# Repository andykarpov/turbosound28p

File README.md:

# Turbosound AVR AY Emul v1.0

TurboSound Emulator on 2x Atmega8A chips based on http://www.avray.ru project.

## How to upload the firmware
Due to there is no room for ISP connectors on the board, you need to solder a few wires directly on the board and connect them with your programmer:
- GND, VCC and RESET signals 
- CK, SO, SI as SCLK, MISO and MOSI signals 
- Do not forget to bridge solder jumpers

### Uploading:

Use avrdude and USBAsp programmer to upload firmware for each chip:

avrdude -p atmega8 -c USBasp -U flash:w:emul_230_turbosound_chip0.hex -U eeprom:w:Conf_parallel_24MHz_1_75Mhz.hex -U lfuse:w:0xCE:m -U hfuse:w:0xCF:m

avrdude -p atmega8 -c USBasp -U flash:w:emul_230_turbosound_chip1.hex -U eeprom:w:Conf_parallel_24MHz_1_75Mhz.hex -U lfuse:w:0xCE:m -U hfuse:w:0xCF:m

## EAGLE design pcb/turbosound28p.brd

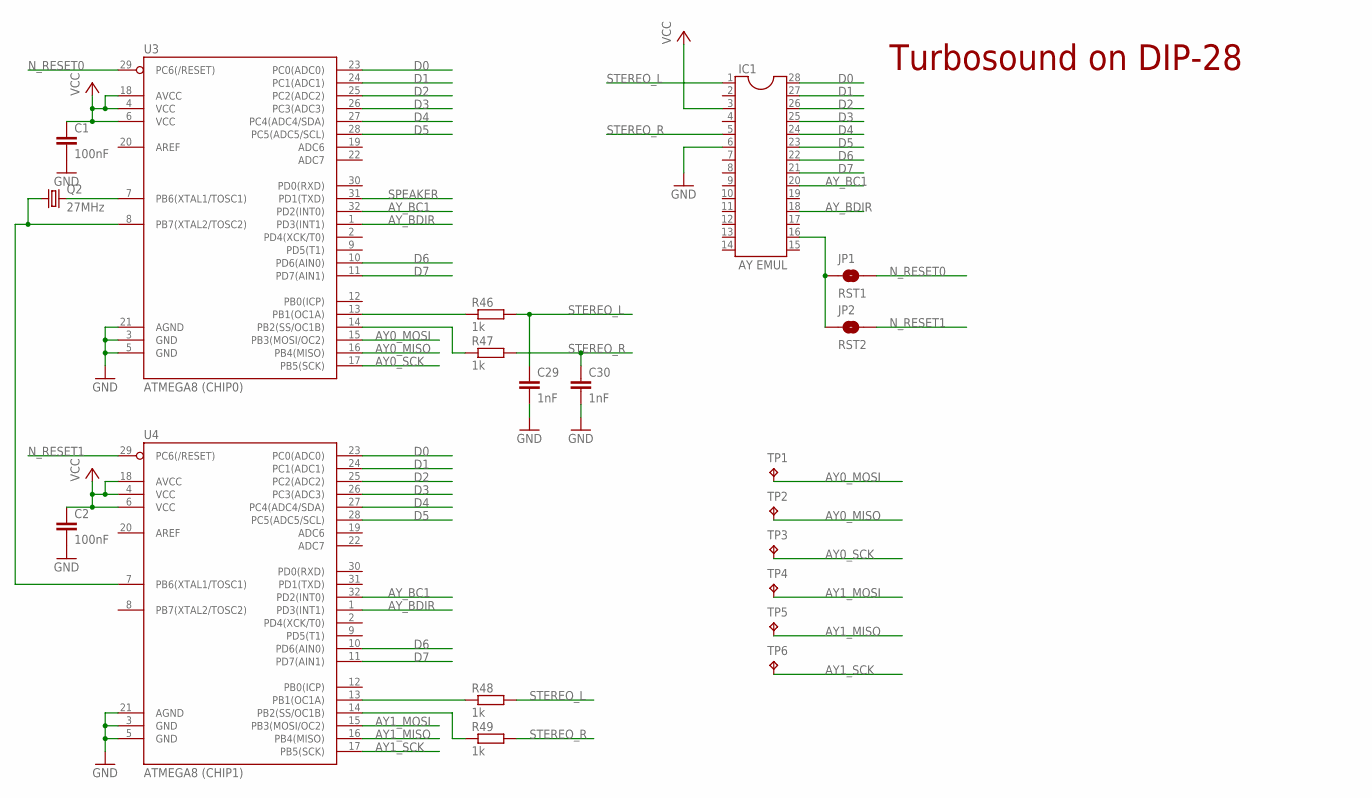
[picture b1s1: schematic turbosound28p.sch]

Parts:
C1, C2: 100nF; C0805
C29, C30: 1nF; C0805
IC1: AY EMUL; DIL28-6
JP1: RST1; SMT-JUMPER_2_NO_SILK
JP2: RST2; SMT-JUMPER_2_NO_SILK
Q2: 27MHz; HC49/S
R46, R47, R48, R49: 1k; R0805
TP1, TP2, TP3, TP4, TP5, TP6: TPB1,27; B1,27
U3: ATMEGA8 (CHIP0); TQFP32-08
U4: ATMEGA8 (CHIP1); TQFP32-08

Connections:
AY0_MISO: TP2.TP, U3.16 (PB4(MISO))
AY0_MOSI: TP1.TP, U3.15 (PB3(MOSI/OC2))
AY0_SCK: TP3.TP, U3.17 (PB5(SCK))
AY1_MISO: TP5.TP, U4.16 (PB4(MISO))
AY1_MOSI: TP4.TP, U4.15 (PB3(MOSI/OC2))
AY1_SCK: TP6.TP, U4.17 (PB5(SCK))
AY_BC1: IC1.20, U3.32 (PD2(INT0)), U4.32 (PD2(INT0))
AY_BDIR: IC1.18, U3.1 (PD3(INT1)), U4.1 (PD3(INT1))
D0: IC1.28, U3.23 (PC0(ADC0)), U4.23 (PC0(ADC0))
D1: IC1.27, U3.24 (PC1(ADC1)), U4.24 (PC1(ADC1))
D2: IC1.26, U3.25 (PC2(ADC2)), U4.25 (PC2(ADC2))
D3: IC1.25, U3.26 (PC3(ADC3)), U4.26 (PC3(ADC3))
D4: IC1.24, U3.27 (PC4(ADC4/SDA)), U4.27 (PC4(ADC4/SDA))
D5: IC1.23, U3.28 (PC5(ADC5/SCL)), U4.28 (PC5(ADC5/SCL))
D6: IC1.22, U3.10 (PD6(AIN0)), U4.10 (PD6(AIN0))
D7: IC1.21, U3.11 (PD7(AIN1)), U4.11 (PD7(AIN1))
GND: C1.2, C2.2, C29.2, C30.2, IC1.6, U3.3 (GND), U3.5 (GND), U3.21 (AGND), U4.3 (GND), U4.5 (GND), U4.21 (AGND)
unnamed: IC1.16, JP1.1, JP2.1
unnamed: R46.1, U3.13 (PB1(OC1A))
unnamed: R47.1, U3.14 (PB2(SS/OC1B))
unnamed: Q2.2, U3.7 (PB6(XTAL1/TOSC1))
unnamed: Q2.1, U3.8 (PB7(XTAL2/TOSC2)), U4.7 (PB6(XTAL1/TOSC1))
unnamed: R48.1, U4.13 (PB1(OC1A))
unnamed: R49.1, U4.14 (PB2(SS/OC1B))
N_RESET0: JP1.2, U3.29 (PC6(/RESET))
N_RESET1: JP2.2, U4.29 (PC6(/RESET))
SPEAKER: U3.31 (PD1(TXD))
STEREO_L: C29.1, IC1.1, R46.2, R48.2
STEREO_R: C30.1, IC1.5, R47.2, R49.2
VCC: C1.1, C2.1, IC1.3, U3.4 (VCC), U3.6 (VCC), U3.18 (AVCC), U4.4 (VCC), U4.6 (VCC), U4.18 (AVCC)

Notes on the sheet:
Turbosound on DIP-28

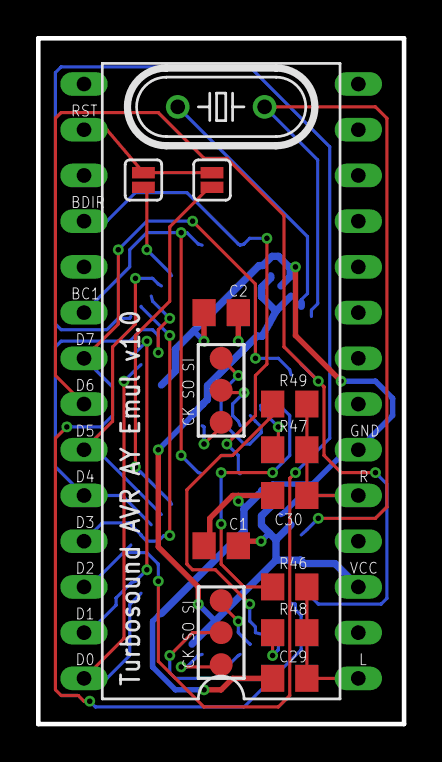
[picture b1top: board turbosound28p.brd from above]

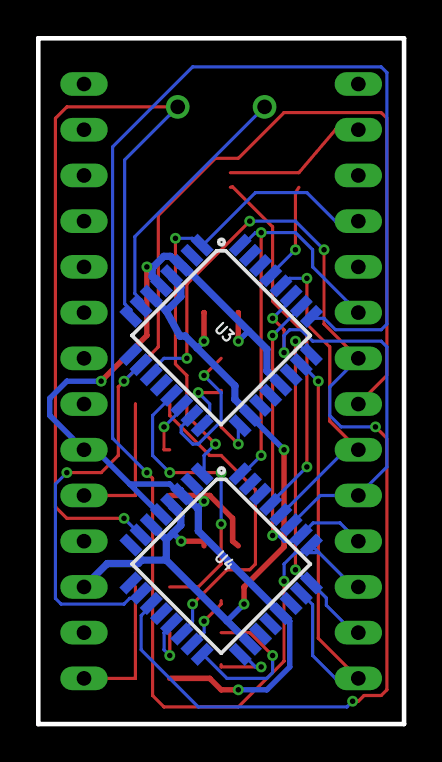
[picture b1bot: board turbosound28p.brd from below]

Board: 2 copper layers, 20.3 x 38.1 mm, 20 parts (2 on the bottom side), 29 nets.

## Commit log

2019-03-05 README
2019-03-05 Turbosound firmware
2019-03-05 PCB sources and gerbers
2019-03-05 added photos
2019-03-05 Added schematics pdf
2019-03-05 Cosmetics
2019-09-26 Added eeprom config for 1.77MHz clock (untested)
2019-09-26 ver 24.7

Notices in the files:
parts and their libraries:
SparkFun-IC-Microcontroller: Licensing: Creative Commons ShareAlike 4.0 International - https://creativecommons.org/licenses/by-sa/4.0
